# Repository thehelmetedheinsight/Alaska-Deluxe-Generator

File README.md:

## Alaska-Deluxe-Generator

Updated: 1/7/2026

Prototype boards received 1/8/26 - Testing started...
- 1/13/26 I have already noted several design changes which will require another production run before release
  - Timeframes should be able to be met as planned. (Q1-Q2 2026)

Pre-orders coming very soon (getting closer, just a few more days)

ko-fi: heinsight
https://ko-fi.com/heinsight

### A Self-Contained Laboratory Grade Colloidal Generator - For Alaska *and beyond*.

#### First, let's get the legal stuff out of the way: Located here are plans for a device intended to generate nanoparticles (1-5 micron is ideal) in an ionically stable aqueous solution. This product is not intended to treat, or cure any disease. How you use the solution that *you* make (operated according to specifications) is entirely up to you. Do your own research, Take responsibility for your own health> Use at your own discretion. There can be risks involved in anything. You are responsible. No links or referenes posted here are meant to recommend, endorse, advocate, advertise, or promote any specific protocol for your own uses. These are items you must determine. WE will make a good device with default setting that are "safe" for people who use stuff without reading the directions. Thank you for your attention to these things.

And now...

#### Our goal is for you to have the ability to produce *excellent quality* colloidal products when alternatives are inferior, difficult to obtain, or unavailable. *THIS* device produces solutions that are far superior to any pressed pill, maximizing bioavailability with extremely low contaminants. You can achieve the highest level of satisfaction by reading ALL the documentation and instructions that we will provide.

****The hardware is designed to give you a complete colloidal electrolysis workshop.****
For the DIY inclined, purchase the board and download the CAD/STL/STEP/Board measurement files (for free) and print your own case, your own design. Print it the way you like.
You can choose your own battery chemistry and size.
You can modify the code we provide on your own. Change it, upload it. No restrictions. No planned obsolecense.
If you break the screen, order another, open the case, and swap out broken one.

As you can see below, there is a lot of pixel space to be organized and utilized more fully.
The screen is 128x64. We will *try* to have intuitive icons and symbols, fast updates, and pragmatic logical information at a glance. Again, you can customize as you wish.

```
┌──────────────────────────────────────────────┐
│       Colloidal Electrolysis Workshop        │
│                                              │
│  Out: 27.5 V     15.10 mA    5.3 W           │
│  Polarity: FORWARD                           │
│                                              │
│  Start set: 17.5V   Time: 60min              │
│  Elapsed:  00:27:14                          │
│  Remaining: 00:32:46                         │
│  ██████████░░░░░░░░░  45%                     │
│                                              │
│  Press selector to stop                      │
└──────────────────────────────────────────────┘
```
You can use this device to read the advertized capabilities of any PD device that uses USB-C connector
- The hardware supports full analysis of PD sources which is good to have around.
```
┌──────────────────────────────────────────────┐
│               PD Input Report                │
│                                              │
│  PD Input Advertisement:                     │
│                                              │
│  5V: 2A                                      │
│  9V: 3A                                      │
│  12V: 5A                                     │
│  15V: 3A                                     │
│  20V: 5A                                     │
│                                              │
│  Press selector to return to menu            │
└──────────────────────────────────────────────┘
```

### Some cool features we have already: (Not in order of priority)
- Built on the reliable ESP32-S3-Mini1 MCU with
- Full RF Certification
- Ultra-low power capabilitity, Dual-core processor
- Designed to take either PD or battery input
- Awesome battery charging: limit LiIon/LiPo "full" charge between 20%-90% to prolong battery health
- Rugged USB-C interface - Durable long life use!
- Sturdy/Rugged rotary encoder button (ALPS EC11)
- WAGO - Top quality rugged electrode socket (Made in USA)
- Field replacable OLED screen 128x64px
- Super accurate power measurement and monitoring
- Robust programmable battery charging and protection controllable in menu 
- Full PD compliant input options - auto selecting input votage from available PD up to 20V
- Full power protection of electronics - from PD/battery input to electrode output
- Super accurate power measurement capabilities which *allow* TONS of cool features:
  - Internal battery power input measurement and charging with charging profile control (TP5100)
  - PD input query (STB4500) and display from the PD source (ex. 5v,9v, 12v, 15v, 20v)
  - Power Output feedback measurement from/to the electrodes (INA226) (Realtime capable)
- Continuous, dynamically adjustable power from menu, leveraging the MCP4017, XL6019, DRV8872
  - MCP4017 digital variable resistor for fine grained power output
  - XL6019 provides boost/buck to handle input range and provide stable output
  - DRV8872 allows for flipping the polarity of the electrodes to eliminate buildup, and produce the smallest partcles and cleanest solution
- Ambient temperature sensor for accurate calibration of electrolysis process AND to monitor 2 battery temperature sensors
- Automatic conductivity measurment for accurate addition of electrolyte (example: Add 7 drops, measure, add 2 drops, measure, etc.)
- Accurate monitoring of solution *prior to and during* the process to calculate the PPM level and progress, time to complete, and stop when PPM reached
- RGB LED for signalling status - many, many colors to choose from (ex. RED=ERROR, colors friendly to "color blindness", and blinky/flashing)
- buzzer/beeper to signal stuff - start/stop/warning also helps visually impared and maybe Dogs
- *AUTO SHUTOFF* if power goes out of spec (ex. a shorted electrode contition during OUTPUT, or a power fault from INPUT, battery fault)
- Modular/modifiable battery configuration: 1x 4.8V or 2x 4.8V (8.4v) cells. Choose your battery chemistry (18650 LiION, prismatic)
- Note: battery options are built into the design, adding a battery is an optional upgrade
- RGB LED to signal ready, generating, finished, and warning. maybe other signals

****A Note about why I did not add a battery****
TLDR: Yes, you can do it with this board. But it's cheaper/easier to buy a battery bank with good PD support.

The onboard battery explanation: In my wild dream, I thought about adding a battery on board that someone would one day want to buy this and stash it in an off-grid cabin. I imagined a 100w solar panel and this seasonal cabin may be uninhabited for 6-9 months at a time. Knowing what I know about the ESP32 S3 and deep sleep mode, it would be totally possible to expect a good amount of the charge to still be available upon returning to the cabin and needing some colloidal copper, or silver. So, I did choose the components to make this a real possibility. However, for the prototypes I dropped the integration of an on-board battery to soften the initial hardware investment and focused on the USB-C and PD (Power Delivery). This was after I had spent time researching (costs) 10k to 25k mAh portable battery banks. There are several models available (Anker, UGREEN, INIU, Scharge Shargeek) supporting great PD (5V,9V,12V,15V,20V) at 45W+ that would provide 20V at minimum 1.5A which is sufficient for running the unit for several batch cycles. Expect at least 5 Gallons (20x 1qt. mason jar cycles) with a 25,000 mAh battery pack before needing recharge.

***
### Features that will be appearing in a short time:
- NEAT-O http interface - to manage, to monitor, and maybe a lot of other things to extend functionality
  - I'm thinking a colloidal generator farm with at least 20 units running simultaneously output 5gal/hr.
- WiFi hostAP mode or WiFi client to connect to home network
- QR code on screen with unique pseudo-random password for local Host AP mode connection - sort of a layer of security
- Customizable recipe scripts easily uploadable via web interface - *Multiple options of nano-particle colloidals*
- Auto shutoff (early) if PPM is achieved before cycle end
- Battery Consumption Management - utilize Ultra Low Power (ULP) standby mode to extend battery readiness time
- HomeAssistant integration - this may also enable hearing impaired folks where the buzzer is not useful
- Batch management for HomeAssistant - Type of colloidal and stock on hand
- Bluetooth pairing sequence - for smartphone app (Release TBD) - also to aid hearing impaired via phone haptic feedback
- Logging of batch production for analysis - possible label or QR code generation linking to the batch logs
- Logging of battery charge/energy usage for the ultra OCD perfectionists, engineers, modifications, etc.

***
### Some ideas for "flashy" attractive things that humans like:
- Cool case designs - As many as are useful, creators retain full credit for work
- extendable to multi-unit production farm for bulk production
  
***
### First pre-production release (very soon Q1-Q2 2026)
- Hardware design (alpha version) FINISHED
- Full KiCad project FINISHED (schematic + PCB, gerbers, BOM, CPL)
- ESP32-S3 firmware IN PROGRESS
- 3D STL case FINISHED
- Mason-jar mouting lid/bracket in STL (3D printable format) IN PROGRESS

***
### Needed:
- Repository of swanky user submitted case designs for easy 3D printing
- A logo or something unique to give identity

I would like to offer "Custom assembled" beta versions of the hardware if you just can't wait for a production unit.
These would be for contributing members of this project, money, or crypto would be an acceptable contribution.
    
```
Alaska Series Colloidal Generator – Terrestrial Development Edition
Copyright (C) 2025 Nathan Hein

This program is free software: you can redistribute it and/or modify
it under the terms of the GNU General Public License version 3 as
published by the Free Software Foundation.

This program is distributed in the hope that it will be useful,
but WITHOUT ANY WARRANTY; without even the implied warranty of
MERCHANTABILITY or FITNESS FOR A PARTICULAR PURPOSE.
See the GNU General Public License for more details.

You should have received a copy of the GNU General Public License
along with this program. If not, see <https://www.gnu.org/licenses/gpl-3.0.html>.

Co-designed with Heinsight and some help from Grok (xAI) – November 2025

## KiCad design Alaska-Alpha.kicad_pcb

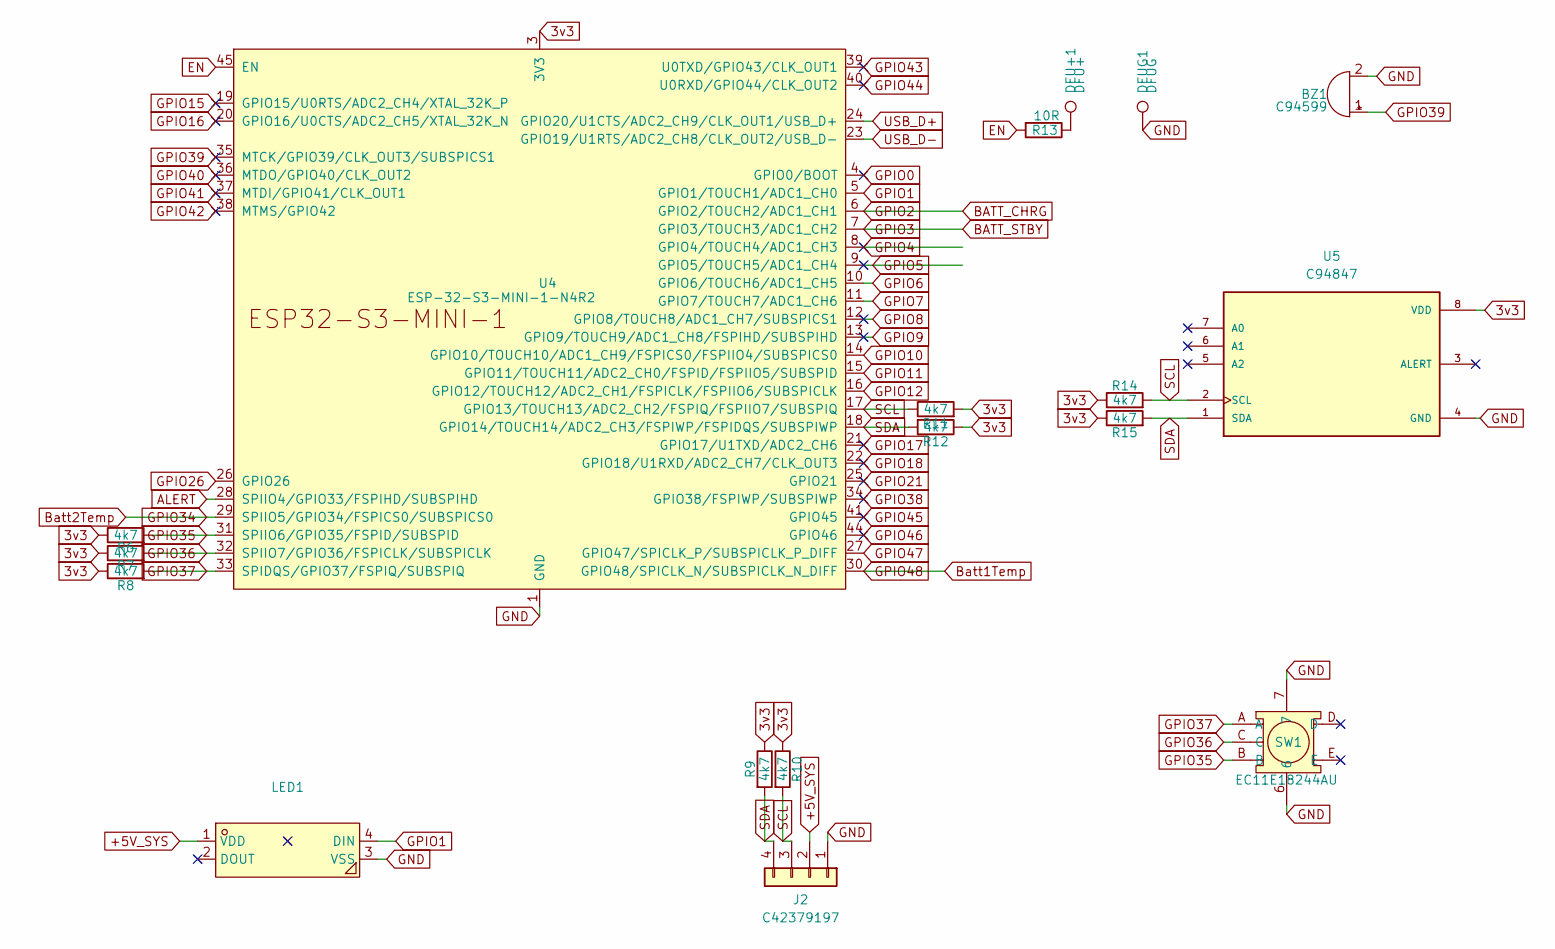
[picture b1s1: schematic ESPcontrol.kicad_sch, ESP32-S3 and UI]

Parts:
BZ1: C94599; BUZ-SMD_4P-L8.5-W8.5-P8.50-BR
DFU+1: DFU+; TestPoint_Pad_2.0x2.0mm
DFUG1: DFUG; TestPoint_Pad_2.0x2.0mm
J2: C42379197; HDR-SMD_HX-PM2.54-1X4P-TP-YQ
LED1: WS2812C; LED-SMD_4P-L5.0-W5.0-LS5.4-TL-1; LCSC Part C114587
R6, R7, R8, R9, R10, R11, R12, R14, R15: 4k7; R_0402_1005Metric
R13: 10R; R_0402_1005Metric
SW1: EC11E18244AU; SW-TH_EC11XXXXXXXX; LCSC Part C202365
U4: ESP-32-S3-MINI-1-N4R2; ESP32-S3-MINI-1; LCSC Part C3013941
U5: C94847; MSOP-8_L3.0-W3.0-P0.65-LS4.9-BL

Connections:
3v3: R6.1, R7.1, R8.1, R9.1, R10.1, R11.2, R12.1, R14.1, R15.1, U4.3 (3V3), U5.8 (VDD); also elsewhere on the board
+5V_SYS: J2.2, LED1.1 (VDD); also elsewhere on the board
ALERT: U4.28 (SPIIO4/GPIO33/FSPIHD/SUBSPIHD); also elsewhere on the board
BATT_CHRG: U4.6 (GPIO2/TOUCH2/ADC1_CH1); also elsewhere on the board
BATT_STBY: U4.7 (GPIO3/TOUCH3/ADC1_CH2); also elsewhere on the board
Batt1Temp: U4.30 (GPIO48/SPICLK_N/SUBSPICLK_N_DIFF); also elsewhere on the board
Batt2Temp: U4.29 (SPIIO5/GPIO34/FSPICS0/SUBSPICS0); also elsewhere on the board
EN: R13.2, U4.45 (EN)
GND: BZ1.2 (-), DFUG1.1, J2.1, LED1.3 (VSS), SW1.6, SW1.7, U4.1 (GND), U4.2 (GND), U4.42 (GND), U4.43 (GND), U4.46 (GND), U4.47 (GND), U4.48 (GND), U4.49 (GND), U4.50 (GND), U4.51 (GND), U4.52 (GND), U4.53 (GND), U4.54 (GND), U4.55 (GND), U4.56 (GND), U4.57 (GND), U4.58 (GND), U4.59 (GND), U4.60 (GND), U4.61 (GND), U4.62 (GND), U4.63 (GND), U4.64 (GND), U4.65 (GND), U5.4 (GND); also elsewhere on the board
GPIO0: U4.4 (GPIO0/BOOT)
GPIO1: LED1.4 (DIN), U4.5 (GPIO1/TOUCH1/ADC1_CH0)
GPIO4: U4.8 (GPIO4/TOUCH4/ADC1_CH3)
GPIO5: U4.9 (GPIO5/TOUCH5/ADC1_CH4)
GPIO6: U4.10 (GPIO6/TOUCH6/ADC1_CH5); also elsewhere on the board
GPIO7: U4.11 (GPIO7/TOUCH7/ADC1_CH6); also elsewhere on the board
GPIO8: U4.12 (GPIO8/TOUCH8/ADC1_CH7/SUBSPICS1)
GPIO9: U4.13 (GPIO9/TOUCH9/ADC1_CH8/FSPIHD/SUBSPIHD)
GPIO10: U4.14 (GPIO10/TOUCH10/ADC1_CH9/FSPICS0/FSPIIO4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); also elsewhere on the board
GPIO11: U4.15 (GPIO11/TOUCH11/ADC2_CH0/FSPID/FSPIIO5/S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); also elsewhere on the board
GPIO12: U4.16 (GPIO12/TOUCH12/ADC2_CH1/FSPICLK/FSPIIO6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)
GPIO15: U4.19 (GPIO15/U0RTS/ADC2_CH4/XTAL_32K_P)
GPIO16: U4.20 (GPIO16/U0CTS/ADC2_CH5/XTAL_32K_N)
GPIO17: U4.21 (GPIO17/U1TXD/ADC2_CH6)
GPIO18: U4.22 (GPIO18/U1RXD/ADC2_CH7/CLK_OUT3)
GPIO21: U4.25 (GPIO21)
GPIO26: U4.26 (GPIO26); also elsewhere on the board
GPIO35: R6.2, SW1.B, U4.31 (SPIIO6/GPIO35/FSPID/SUBSPID)
GPIO36: R7.2, SW1.C, U4.32 (SPIIO7/GPIO36/FSPICLK/SUBSPICLK)
GPIO37: R8.2, SW1.A, U4.33 (SPIDQS/GPIO37/FSPIQ/SUBSPIQ)
GPIO38: U4.34 (GPIO38/FSPIWP/SUBSPIWP)
GPIO39: BZ1.1 (+), U4.35 (MTCK/GPIO39/CLK_OUT3/SUBSPICS1)
GPIO40: U4.36 (MTDO/GPIO40/CLK_OUT2)
GPIO41: U4.37 (MTDI/GPIO41/CLK_OUT1)
GPIO42: U4.38 (MTMS/GPIO42)
GPIO43: U4.39 (U0TXD/GPIO43/CLK_OUT1)
GPIO44: U4.40 (U0RXD/GPIO44/CLK_OUT2)
GPIO45: U4.41 (GPIO45)
GPIO46: U4.44 (GPIO46)
GPIO47: U4.27 (GPIO47/SPICLK_P/SUBSPICLK_P_DIFF); also elsewhere on the board
unnamed: DFU+1.1, R13.1
SCL: J2.3, R10.2, R11.1, R14.2, U4.17 (GPIO13/TOUCH13/ADC2_CH2/FSPIQ/FSPIIO7/S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), U5.2 (SCL); also elsewhere on the board
SDA: J2.4, R9.2, R12.2, R15.2, U4.18 (GPIO14/TOUCH14/ADC2_CH3/FSPIWP/FSPIDQS/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), U5.1 (SDA); also elsewhere on the board
USB_D+: U4.24 (GPIO20/U1CTS/ADC2_CH9/CLK_OUT1/USB_D+); also elsewhere on the board
USB_D-: U4.23 (GPIO19/U1RTS/ADC2_CH8/CLK_OUT2/USB_D-); also elsewhere on the board

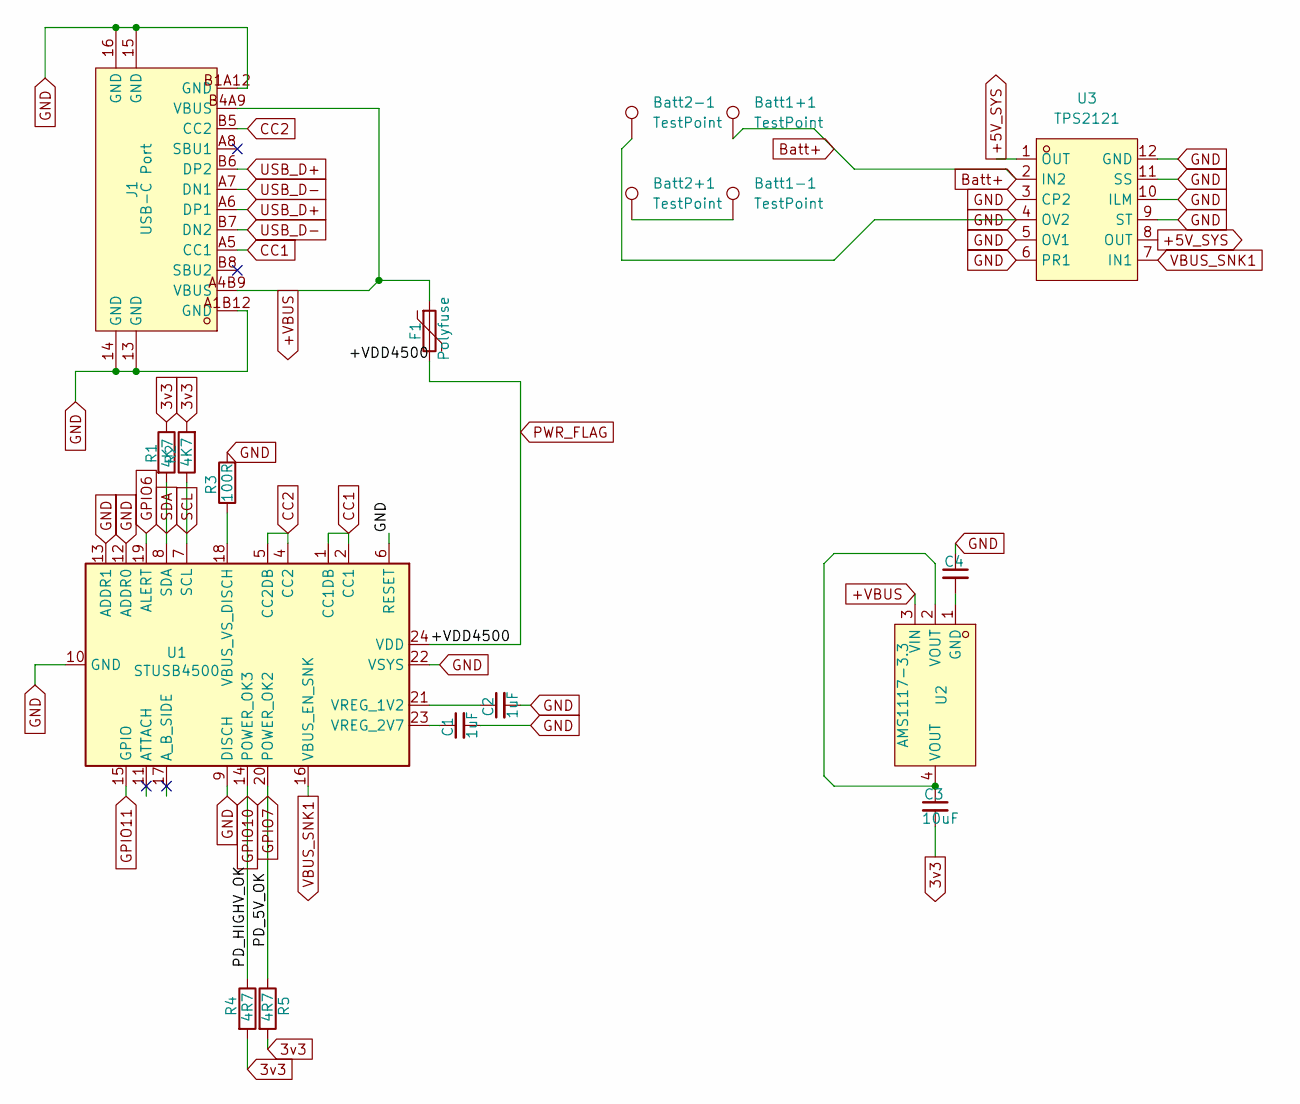
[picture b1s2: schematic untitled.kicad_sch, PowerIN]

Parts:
Batt1+1, Batt1-1, Batt2+1, Batt2-1: TestPoint; TestPoint_Pad_2.0x2.0mm
C1, C2: 1uF; C1206
C3, C4: 10uF; C1206
F1: Polyfuse; R0805; LCSC Part C207019
J1: USB-C Port; MICRO-USB-SMD_GT-USB-7047B; LCSC Part C963217
R1, R2: 4K7; R_0402_1005Metric
R3: 100R; R_0402_1005Metric
R4, R5: 4R7; R_0402_1005Metric
U1: STUSB4500; QFN-24_L4.0-W4.0-P0.50-BL-EP2.8; LCSC Part C2678061
U2: AMS1117-3.3; SOT-223-3_L6.5-W3.4-P2.30-LS7.0-BR; LCSC Part C6186
U3: TPS2121; VQFN-HR-12_L2.5-W2.0-P0.50-BL; LCSC Part C485916

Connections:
3v3: C3.2, R1.1, R2.2, R4.2, R5.2; also elsewhere on the board
+5V_SYS: U3.1 (OUT), U3.8 (OUT); also elsewhere on the board
+VBUS: F1.1, J1.A4B9 (VBUS), J1.B4A9 (VBUS), U2.3 (VIN)
Batt+: Batt1+1.1, U3.2 (IN2); also elsewhere on the board
CC1: J1.A5 (CC1), U1.1 (CC1DB), U1.2 (CC1)
CC2: J1.B5 (CC2), U1.4 (CC2), U1.5 (CC2DB)
GND: Batt2-1.1, C1.2, C2.2, C4.1, J1.13 (GND), J1.14 (GND), J1.15 (GND), J1.16 (GND), J1.A1B12 (GND), J1.B1A12 (GND), R3.2, U1.6 (RESET), U1.9 (DISCH), U1.10 (GND), U1.12 (ADDR0), U1.13 (ADDR1), U1.22 (VSYS), U1.25 (GND), U3.3 (CP2), U3.4 (OV2), U3.5 (OV1), U3.6 (PR1), U3.9 (ST), U3.10 (ILM), U3.11 (SS), U3.12 (GND); also elsewhere on the board
GPIO6: U1.19 (ALERT); also elsewhere on the board
GPIO7: R5.1, U1.20 (POWER_OK2); also elsewhere on the board
GPIO10: R4.1, U1.14 (POWER_OK3); also elsewhere on the board
GPIO11: U1.15 (GPIO); also elsewhere on the board
unnamed: Batt1-1.1, Batt2+1.1
unnamed: C3.1, U2.2 (VOUT), U2.4 (VOUT)
unnamed: R3.1, U1.18 (VBUS_VS_DISCH)
unnamed: C2.1, U1.21 (VREG_1V2)
unnamed: C1.1, U1.23 (VREG_2V7)
unnamed: C4.2, U2.1 (GND)
PWR_FLAG: F1.2, U1.24 (VDD)
SCL: R2.1, U1.7 (SCL); also elsewhere on the board
SDA: R1.2, U1.8 (SDA); also elsewhere on the board
USB_D+: J1.A6 (DP1), J1.B6 (DP2); also elsewhere on the board
USB_D-: J1.A7 (DN1), J1.B7 (DN2); also elsewhere on the board
VBUS_SNK1: U1.16 (VBUS_EN_SNK), U3.7 (IN1)

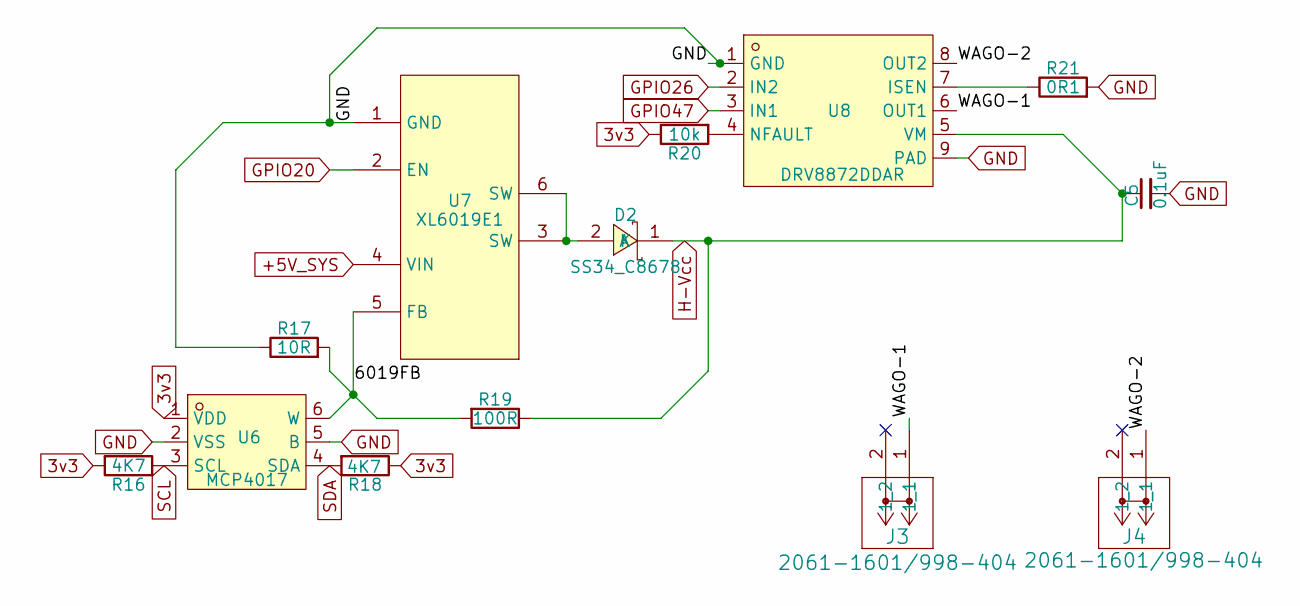
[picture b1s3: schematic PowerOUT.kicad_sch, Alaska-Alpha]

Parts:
C5: 0.1uF; C1206
D2: SS34_C8678; SMA_L4.3-W2.6-LS5.2-RD; LCSC Part C8678
J3, J4: 2061-1601/998-404; 2061-601&slash_998-404
R16, R18: 4K7; R_0402_1005Metric
R17: 10R; R_0402_1005Metric
R19: 100R; R_0402_1005Metric
R20: 10k; R_0402_1005Metric
R21: 0R1; R_0402_1005Metric
U6: MCP4017; SC-70-6_L2.2-W1.3-P0.65-LS2.1-BR; LCSC Part C623396
U7: XL6019E1; TO-263-5_L10.2-W9.9-P1.70-LS14.4-TL; LCSC Part C73018
U8: DRV8872DDAR; HSOP-8_L5.0-W4.0-P1.27-LS6.2-BL-EP; LCSC Part C114179

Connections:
3v3: R16.2, R18.1, R20.1, U6.1 (VDD); also elsewhere on the board
+5V_SYS: U7.4 (VIN); also elsewhere on the board
/PowerOUT/6019FB: R17.2, R19.2, U6.6 (W), U7.5 (FB)
/PowerOUT/WAGO-1: J3.1 (1_1), U8.6 (OUT1)
/PowerOUT/WAGO-2: J4.1 (1_1), U8.8 (OUT2)
GND: C5.2, R17.1, R21.2, U6.2 (VSS), U6.5 (B), U7.1 (GND), U8.1 (GND), U8.9 (PAD); also elsewhere on the board
GPIO20: U7.2 (EN)
GPIO26: U8.2 (IN2); also elsewhere on the board
GPIO47: U8.3 (IN1); also elsewhere on the board
H-Vcc: C5.1, D2.1 (K), R19.1, U8.5 (VM); also elsewhere on the board
unnamed: D2.2 (A), U7.3 (SW), U7.6 (SW)
unnamed: R21.1, U8.7 (ISEN)
unnamed: R20.2, U8.4 (NFAULT)
SCL: R16.1, U6.3 (SCL); also elsewhere on the board
SDA: R18.2, U6.4 (SDA); also elsewhere on the board

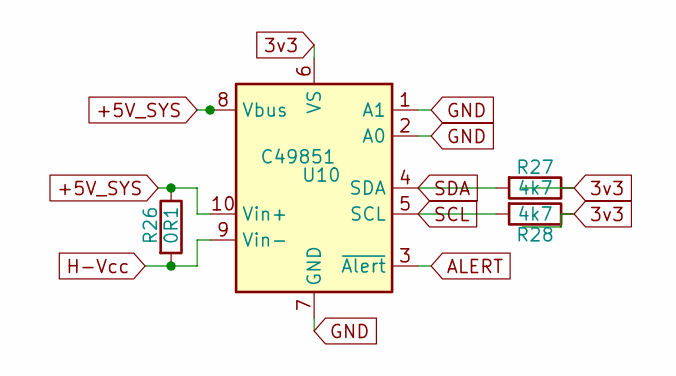
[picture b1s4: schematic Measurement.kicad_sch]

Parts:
R26: 0R1; R_0402_1005Metric
R27, R28: 4k7; R_0402_1005Metric
U10: C49851; MSOP-10_L3.0-W3.0-P0.50-LS5.0-BL

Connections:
3v3: R27.1, R28.1, U10.6 (VS); also elsewhere on the board
+5V_SYS: R26.1, U10.8 (Vbus), U10.10 (Vin+); also elsewhere on the board
ALERT: U10.3 (~Alert); also elsewhere on the board
GND: U10.1 (A1), U10.2 (A0), U10.7 (GND); also elsewhere on the board
H-Vcc: R26.2, U10.9 (Vin-); also elsewhere on the board
SCL: R28.2, U10.5 (SCL); also elsewhere on the board
SDA: R27.2, U10.4 (SDA); also elsewhere on the board

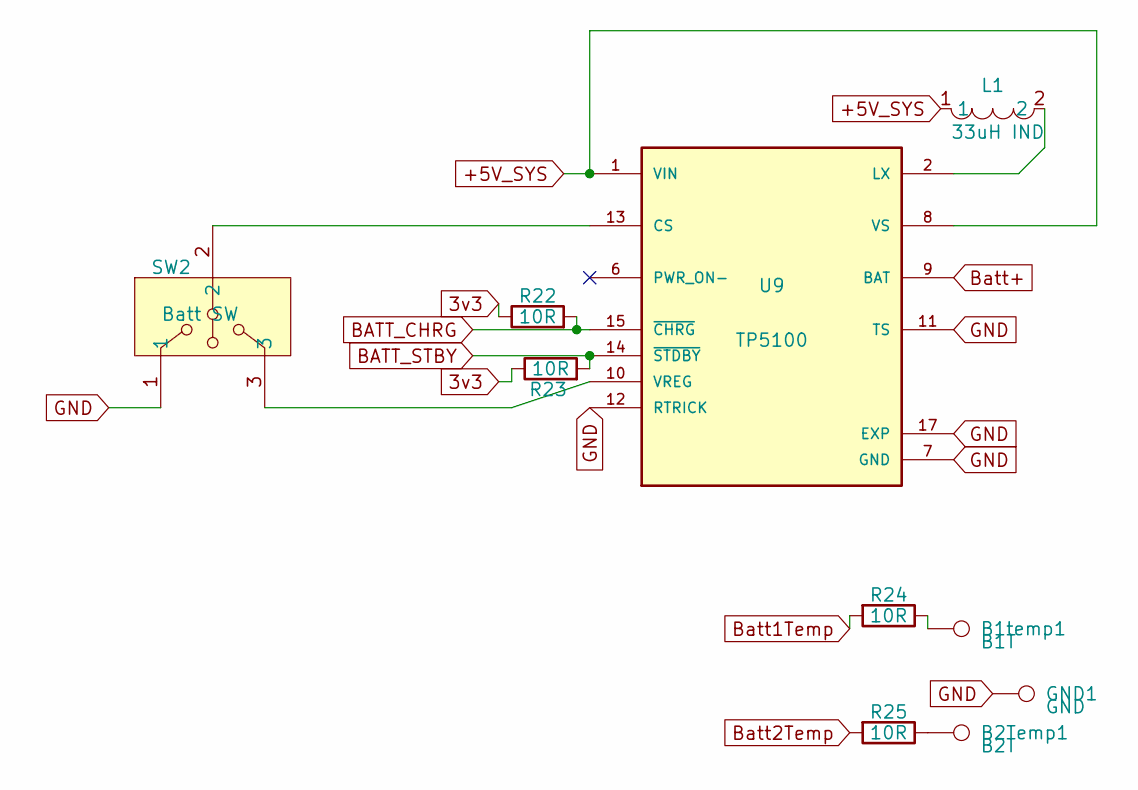
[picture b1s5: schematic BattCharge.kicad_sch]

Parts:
B1temp1: B1T; TestPoint_Pad_2.0x2.0mm
B2Temp1: B2T; TestPoint_Pad_2.0x2.0mm
GND1: GND; TestPoint_Pad_2.0x2.0mm
L1: 33uH IND; IND-SMD_L7.1-W6.6_SRP6030VA; LCSC Part C22463826
R22, R23, R24, R25: 10R; R_0402_1005Metric
SW2: Batt SW; SW-SMD_CJS-1201B; LCSC Part C132858
U9: TP5100; TQFN-16_L4.0-W4.0-P0.65-BL-EP; LCSC Part C379389

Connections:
3v3: R22.1, R23.1; also elsewhere on the board
+5V_SYS: L1.1, U9.1 (VIN), U9.4 (VIN), U9.5 (VIN), U9.8 (VS), U9.16 (VIN); also elsewhere on the board
BATT_CHRG: R22.2, U9.15 (~CHRG); also elsewhere on the board
BATT_STBY: R23.2, U9.14 (~STDBY); also elsewhere on the board
Batt1Temp: R24.2; also elsewhere on the board
Batt2Temp: R25.2; also elsewhere on the board
Batt+: U9.9 (BAT); also elsewhere on the board
GND: GND1.1, SW2.1, U9.7 (GND), U9.11 (TS), U9.12 (RTRICK), U9.17 (EXP); also elsewhere on the board
unnamed: B1temp1.1, R24.1
unnamed: B2Temp1.1, R25.1
unnamed: L1.2, U9.2 (LX), U9.3 (LX)
unnamed: SW2.2, U9.13 (CS)
unnamed: SW2.3, U9.10 (VREG)

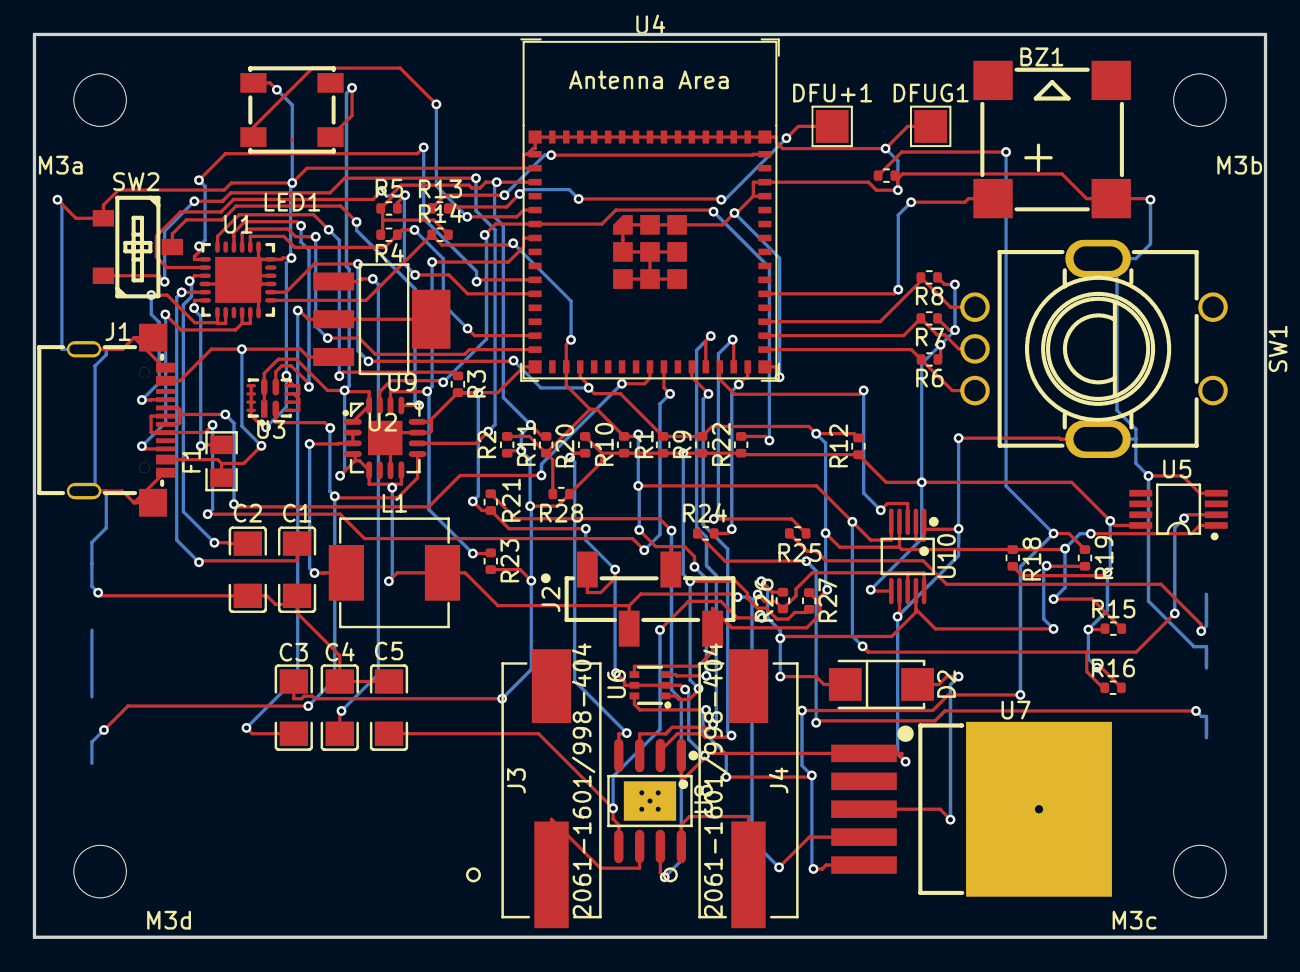
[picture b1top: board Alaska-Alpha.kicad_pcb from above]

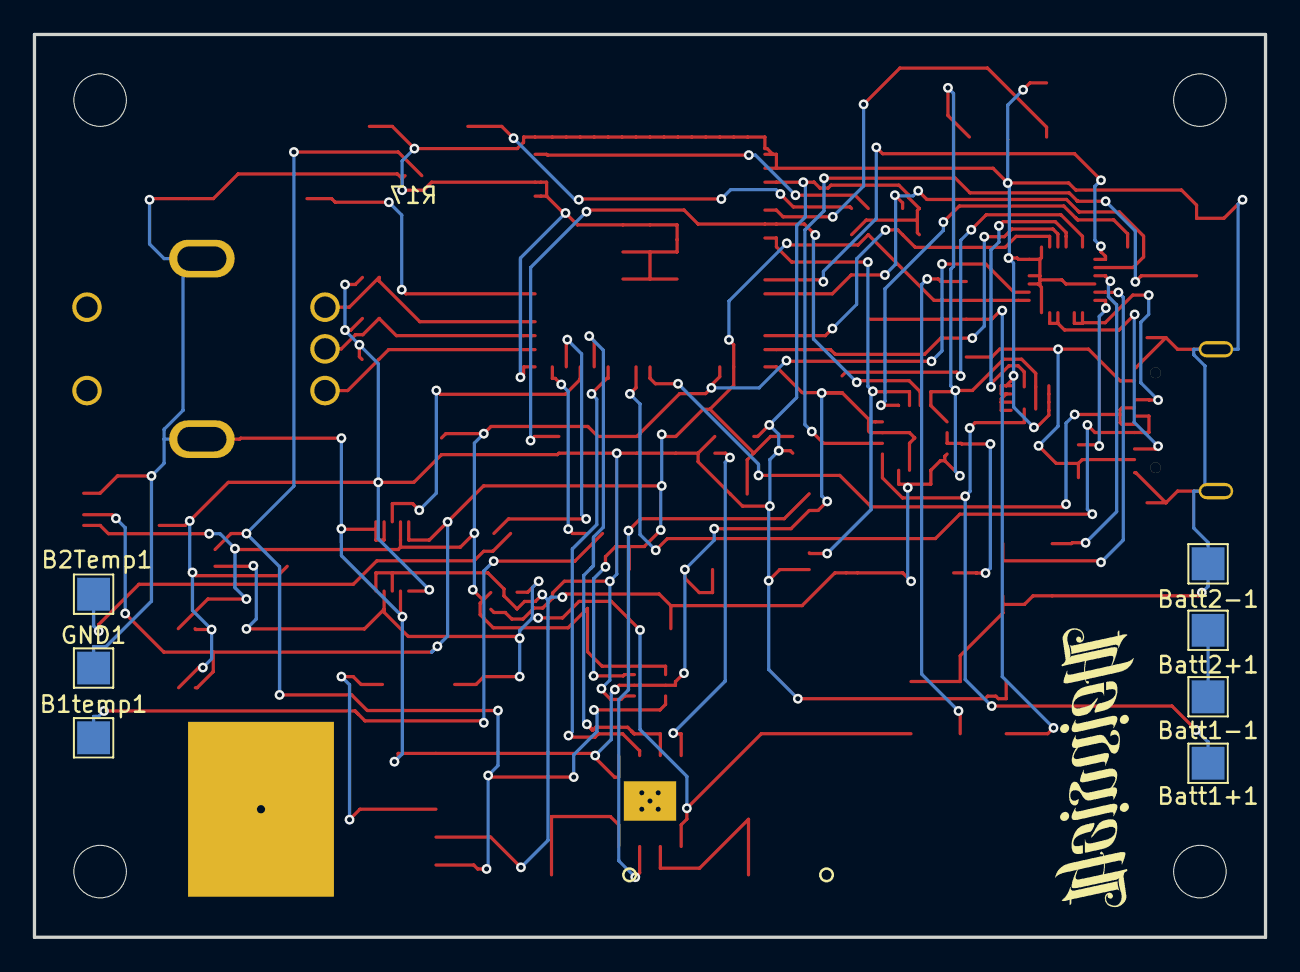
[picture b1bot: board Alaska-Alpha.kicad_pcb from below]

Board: 2 copper layers, 75.0 x 55.0 mm, 67 parts (7 on the bottom side), 49 nets.

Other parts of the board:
M3a, M3b, M3c, M3d: MountingHole_3.2mm_M3

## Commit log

2025-12-26 Add files via upload
    Just a little peek. Work in progress on the routing and fine particulars.
2025-12-26 Update README.md
    Image update
2025-12-27 Update README.md
    Not just Silver, but primarily Copper and also, Gold!
2025-12-27 Update README.md
    Update
2026-01-02 Update README.md
    2026 New Year update
2026-01-02 Add files via upload
    adding the 3D render of board
2026-01-07 Update README.md
    1/7/26 update
2026-01-12 Update README.md
    Prototype board testing begins
2026-01-20 Add Ko-fi username to FUNDING.yml
    Updated funding model to include Ko-fi username.

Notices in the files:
parts and their libraries:
Copyright 2016 Accelerated Designs. All rights reserved.
